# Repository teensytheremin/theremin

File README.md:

# Teensy Theremin

Teensy 4.1 MCU based Digital Theremin

This project is aimed to design of simple but good DIY digital [theremin](https://en.wikipedia.org/wiki/Theremin) based on microcontroller and FPGAs.

Project's documentation is available on [Github Pages](https://teensytheremin.github.io/theremin/)

## Licensing

This is open source open hardware project.

You can freely build device using instructions for personal usage, but cannot sell it.

Firmware is licensed under GPL v2 license.

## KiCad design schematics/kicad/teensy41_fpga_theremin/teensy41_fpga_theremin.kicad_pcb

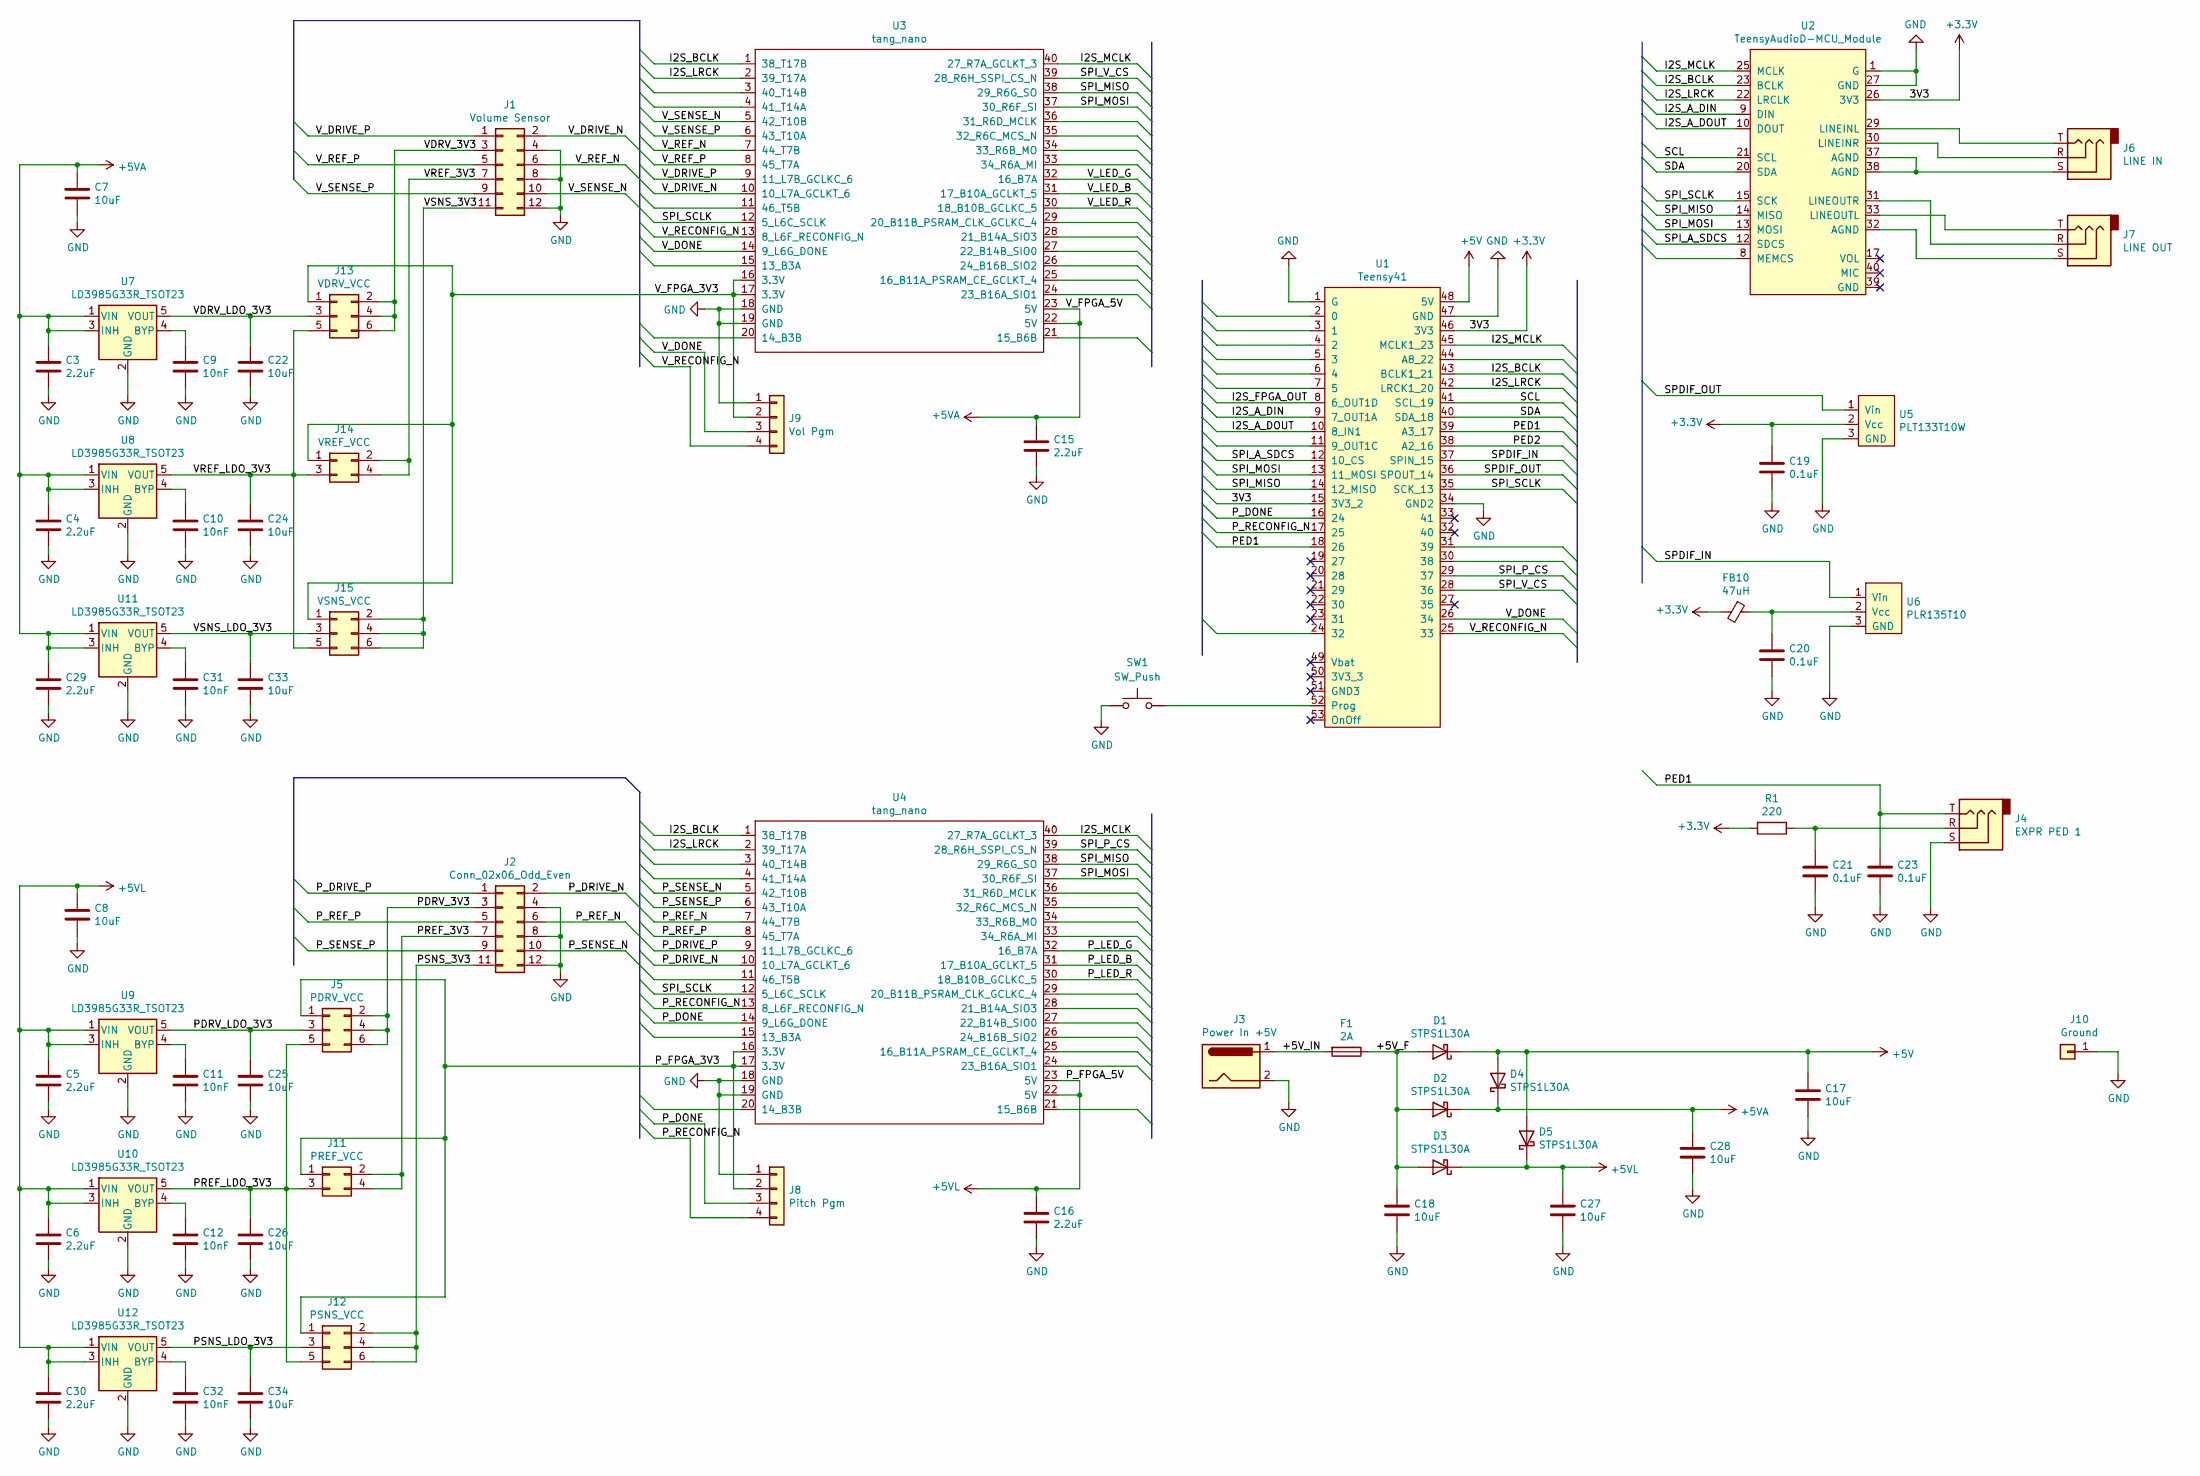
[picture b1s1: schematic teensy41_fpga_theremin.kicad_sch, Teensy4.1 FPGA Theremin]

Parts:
C3, C4, C5, C6, C15, C16, C29, C30: 2.2uF; C_0805_2012Metric
C7, C8, C17, C18, C22, C24, C25, C26, C27, C28, C33, C34: 10uF; C_0805_2012Metric
C9, C10, C11, C12, C31, C32: 10nF; C_0805_2012Metric
C19, C20, C21, C23: 0.1uF; C_0805_2012Metric
D1, D2, D3, D4, D5: STPS1L30A; D_SMA
F1: 2A; Fuse_1206_3216Metric
FB10: 47uH; L_1812_4532Metric
J1: Volume Sensor; PinSocket_2x06_P2.54mm_Horizontal
J2: Conn_02x06_Odd_Even; PinSocket_2x06_P2.54mm_Horizontal
J3: Power In +5V; BarrelJack_Horizontal
J4: EXPR PED 1; Jack_6.35mm_ST_008G_04
J5: PDRV_VCC; PinHeader_2x03_P2.54mm_Vertical
J6: LINE IN; Jack_3.5mm_CUI_SJ1-3533NG_Horizontal
J7: LINE OUT; Jack_6.35mm_ST_008G_04
J8: Pitch Pgm; PinHeader_1x04_P2.54mm_Vertical
J9: Vol Pgm; PinHeader_1x04_P2.54mm_Vertical
J10: Ground; PinHeader_1x01_P2.54mm_Vertical
J11: PREF_VCC; PinHeader_2x02_P2.54mm_Vertical
J12: PSNS_VCC; PinHeader_2x03_P2.54mm_Vertical
J13: VDRV_VCC; PinHeader_2x03_P2.54mm_Vertical
J14: VREF_VCC; PinHeader_2x02_P2.54mm_Vertical
J15: VSNS_VCC; PinHeader_2x03_P2.54mm_Vertical
R1: 220; R_0805_2012Metric
SW1: SW_Push; SW_Tactile_SPST_Angled_PTS645Vx58-2LFS
U1: Teensy41
U2: TeensyAudioD-MCU_Module; TeensyAudioD
U3, U4: tang_nano
U5: PLT133T10W
U6: PLR135T10; PLT133T10W
U7, U8, U9, U10, U11, U12: LD3985G33R_TSOT23; TSOT-23-5

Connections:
+3V3: C19.1, FB10.2, R1.2, U1.15 (3V3_2), U1.46 (3V3), U2.26 (3V3), U5.2 (Vcc)
+5V: C17.1, D1.1 (K), D4.2 (A), D5.2 (A), U1.48 (5V)
+5VA: C3.1, C4.1, C7.1, C15.1, C28.1, C29.1, D2.1 (K), D4.1 (K), U3.22 (5V), U3.23 (5V), U7.1 (VIN), U7.3 (INH), U8.1 (VIN), U8.3 (INH), U11.1 (VIN), U11.3 (INH)
+5VL: C5.1, C6.1, C8.1, C16.1, C27.1, C30.1, D3.1 (K), D5.1 (K), U4.22 (5V), U4.23 (5V), U9.1 (VIN), U9.3 (INH), U10.1 (VIN), U10.3 (INH), U12.1 (VIN), U12.3 (INH)
/+5V_F: C18.1, D1.2 (A), D2.2 (A), D3.2 (A), F1.1
/+5V_IN: F1.2, J3.1
/I2S_A_DIN: U1.9 (7_OUT1A), U2.9 (DIN)
/I2S_A_DOUT: U1.10 (8_IN1), U2.10 (DOUT)
/I2S_BCLK: U1.43 (BCLK1_21), U2.23 (BCLK), U3.1 (38_T17B), U4.1 (38_T17B)
/I2S_FPGA_OUT: U1.8 (6_OUT1D)
/I2S_LRCK: U1.42 (LRCK1_20), U2.22 (LRCLK), U3.2 (39_T17A), U4.2 (39_T17A)
/I2S_MCLK: U1.45 (MCLK1_23), U2.25 (MCLK), U3.40 (27_R7A_GCLKT_3), U4.40 (27_R7A_GCLKT_3)
/PDRV_3V3: J2.3, J5.2, J5.4, J5.6
/PDRV_LDO_3V3: C25.1, J5.3, U9.5 (VOUT)
/PED1: C23.1, J4.T, U1.18 (26), U1.39 (A3_17)
/PED2: U1.38 (A2_16)
/PREF_3V3: J2.7, J11.2, J11.4
/PREF_LDO_3V3: C26.1, J5.5, J11.3, J12.5, U10.5 (VOUT)
/PSNS_3V3: J2.11, J12.2, J12.4, J12.6
/PSNS_LDO_3V3: C34.1, J12.3, U12.5 (VOUT)
/P_DONE: J8.3, U1.16 (24), U4.14 (9_L6G_DONE)
/P_DRIVE_N: J2.2, U4.10 (10_L7A_GCLKT_6)
/P_DRIVE_P: J2.1, U4.9 (11_L7B_GCLKC_6)
/P_FPGA_3V3: J5.1, J8.2, J11.1, J12.1, U4.16 (3.3V), U4.17 (3.3V)
/P_LED_B: U4.31 (17_B10A_GCLKT_5)
/P_LED_G: U4.32 (16_B7A)
/P_LED_R: U4.30 (18_B10B_GCLKC_5)
/P_RECONFIG_N: J8.4, U1.17 (25), U4.13 (8_L6F_RECONFIG_N)
/P_REF_N: J2.6, U4.7 (44_T7B)
/P_REF_P: J2.5, U4.8 (45_T7A)
/P_SENSE_N: J2.10, U4.5 (42_T10B)
/P_SENSE_P: J2.9, U4.6 (43_T10A)
/SCL: U1.41 (SCL_19), U2.21 (SCL)
/SDA: U1.40 (SDA_18), U2.20 (SDA)
/SPDIF_IN: U1.37 (SPIN_15), U6.1 (Vin)
/SPDIF_OUT: U1.36 (SPOUT_14), U5.1 (Vin)
/SPI_A_SDCS: U1.12 (10_CS), U2.12 (SDCS)
/SPI_MISO: U1.14 (12_MISO), U2.14 (MISO), U3.38 (29_R6G_SO), U4.38 (29_R6G_SO)
/SPI_MOSI: U1.13 (11_MOSI), U2.13 (MOSI), U3.37 (30_R6F_SI), U4.37 (30_R6F_SI)
/SPI_P_CS: U1.29 (37), U4.39 (28_R6H_SSPI_CS_N)
/SPI_SCLK: U1.35 (SCK_13), U2.15 (SCK), U3.12 (5_L6C_SCLK), U4.12 (5_L6C_SCLK)
/SPI_V_CS: U1.28 (36), U3.39 (28_R6H_SSPI_CS_N)
/VDRV_3V3: J1.3, J13.2, J13.4, J13.6
/VDRV_LDO_3V3: C22.1, J13.3, U7.5 (VOUT)
/VREF_3V3: J1.7, J14.2, J14.4
/VREF_LDO_3V3: C24.1, J13.5, J14.3, J15.5, U8.5 (VOUT)
/VSNS_3V3: J1.11, J15.2, J15.4, J15.6
/VSNS_LDO_3V3: C33.1, J15.3, U11.5 (VOUT)
/V_DONE: J9.3, U1.26 (34), U3.14 (9_L6G_DONE)
/V_DRIVE_N: J1.2, U3.10 (10_L7A_GCLKT_6)
/V_DRIVE_P: J1.1, U3.9 (11_L7B_GCLKC_6)
/V_FPGA_3V3: J9.2, J13.1, J14.1, J15.1, U3.16 (3.3V), U3.17 (3.3V)
/V_LED_B: U3.31 (17_B10A_GCLKT_5)
/V_LED_G: U3.32 (16_B7A)
/V_LED_R: U3.30 (18_B10B_GCLKC_5)
/V_RECONFIG_N: J9.4, U1.25 (33), U3.13 (8_L6F_RECONFIG_N)
/V_REF_N: J1.6, U3.7 (44_T7B)
/V_REF_P: J1.5, U3.8 (45_T7A)
/V_SENSE_N: J1.10, U3.5 (42_T10B)
/V_SENSE_P: J1.9, U3.6 (43_T10A)
GND: C3.2, C4.2, C5.2, C6.2, C7.2, C8.2, C9.2, C10.2, C11.2, C12.2, C15.2, C16.2, C17.2, C18.2, C19.2, C20.2, C21.2, C22.2, C23.2, C24.2, C25.2, C26.2, C27.2, C28.2, C29.2, C30.2, C31.2, C32.2, C33.2, C34.2, J1.4, J1.8, J1.12, J2.4, J2.8, J2.12, J3.2, J4.S, J8.1, J9.1, J10.1, SW1.1, U1.1 (G), U1.34 (GND2), U1.47 (GND), U2.1 (G), U2.27 (GND), U3.18 (GND), U3.19 (GND), U4.18 (GND), U4.19 (GND), U5.3 (GND), U6.3 (GND), U7.2 (GND), U8.2 (GND), U9.2 (GND), U10.2 (GND), U11.2 (GND), U12.2 (GND)
unnamed: C9.1, U7.4 (BYP)
unnamed: C10.1, U8.4 (BYP)
unnamed: C11.1, U9.4 (BYP)
unnamed: C12.1, U10.4 (BYP)
unnamed: C20.1, FB10.1, U6.2 (Vcc)
unnamed: C21.1, J4.R, R1.1
unnamed: C31.1, U11.4 (BYP)
unnamed: C32.1, U12.4 (BYP)
unnamed: J6.R, U2.30 (LINEINR)
unnamed: J6.S, U2.37 (AGND), U2.38 (AGND)
unnamed: J6.T, U2.29 (LINEINL)
unnamed: J7.R, U2.31 (LINEOUTR)
unnamed: J7.S, U2.32 (AGND)
unnamed: J7.T, U2.33 (LINEOUTL)
unnamed: SW1.2, U1.52 (Prog)

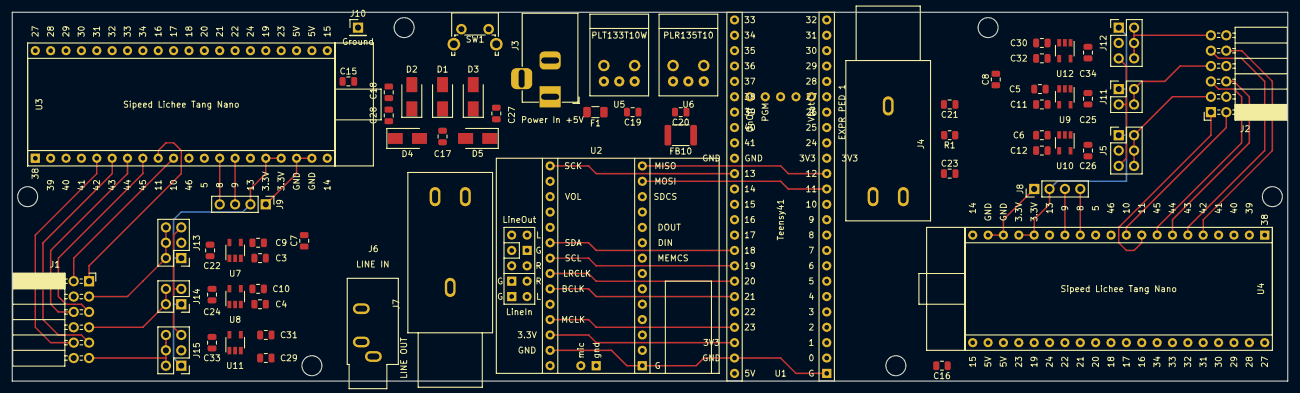
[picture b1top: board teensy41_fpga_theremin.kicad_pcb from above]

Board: 2 copper layers, 210.8 x 61.0 mm, 66 parts (0 on the bottom side), 68 nets.

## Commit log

2021-09-15 Set theme jekyll-theme-tactile
2021-09-15 current sensing comparator sensor simulation
2021-09-15 ltspice model
2021-09-15 sensor page created
2021-09-15 update main page - components to buy
2021-09-15 description
2021-09-15 update description
2021-09-15 config changes
2021-09-15 sensors page
2021-09-15 update sensors page
2021-09-15 ltc6752 oscillator spice model:
2021-09-15 spice model
2021-09-15 add github pages link
2021-09-15 main board kicad project and geerber files
2021-09-16 git ignore for ltspice
2021-09-16 add dester's bjt current sensing oscillator model
2021-09-21 add D flipflop model
2021-09-21 lvc74 lvc86 pll
2021-09-23 pll model
2021-09-24 opamp models, pll schematic
2021-09-27 current sensing pll model
2021-09-27 ltspice simulation
2021-10-11 current sensing oscillator model
2021-10-11 oscillator ltspice images
2021-10-12 current sensing oscillator 04 spice model images
2021-10-12 current sensing oscillator ltspice model 04
2021-10-13 current sensing oscillator 05
2021-10-13 oscillator images 05
2021-10-15 lt6200 current sensing oscillator images
2021-10-15 lt6200 oscillator spice model
2021-10-15 schematics - pdfs and images
2021-10-15 add libraries
2021-10-15 display and controls board
2021-10-15 PCBs
2021-10-15 boards
2021-10-15 sensor pdf links
2021-10-15 update docs
2021-10-16 sensor design
2021-10-22 component spice models
2021-10-22 unbuffered inverter oscillator model
2021-10-22 unbuffered inverter current sensing spice model screenshots
2021-10-27 dual opamps current sensing oscillator model image
2021-10-27 dual opamp current sensing oscillator - ltspice model
2021-10-28 current sensing pll ltspice model
2021-10-28 ltspice component lvc1gx04
2021-10-28 pll oscillator spice model
2021-11-06 current sensing oscillator 8bjts spice model
2021-11-06 oscillator spice model
2021-11-08 pll bjts spice model
2021-11-08 spice model pll oscillator bjts
2021-11-09 current sensing oscillator inverters
2021-11-09 spice model - unbuffered inverters current sensing oscillator
2021-11-10 74hcu04 current sensing oscillator ltspice model
2021-11-10 unbuffered inverter spice models
2021-11-11 inverter spice models
2021-11-11 lvcu04 oscillator ltspice model
2021-11-11 lvcu04 oscillator ltspice model images
2021-11-12 inv and bjt current sensing oscillator model
2021-11-12 current sensing oscillator on inverters and bjt current mirrors - ltspice model
2021-11-17 main hum noise simulation
2021-11-23 xo2 / tinyfpga ax2 theremin sensor implementation - initial commit
2021-11-23 ax2 pins assignment
2021-11-30 teensy fpga cabinet and boards placement / planning
2021-11-30 cabinet drawing
2021-11-30 teensy fpga main board fpga project
2021-11-30 kicad libraries
2021-12-09 cabinet OpenSCAD - part 1
2021-12-09 teensy fpga theremin main pcb
2021-12-09 openscad screenshots
2021-12-10 cabinet design - tablet mounts and antennas
2021-12-10 cabinet images
2021-12-13 openscad cabinet project
2021-12-14 cabinet design - openscad
2021-12-16 tang nano photos
2021-12-16 Initial commit
    A modified PlaySynthMusic example. Testing sound and codec. Prints audio chip id to serial port.
2021-12-17 pcb placement render
2021-12-17 cabinet openscad model:
2021-12-17 Pitch and volume input simulation added
    Using IntervalTimer to simulate pitch and volume input from sensors. Volume control now works. Sensor values are printed to serial port.
2021-12-20 fittings
2021-12-22 Generating sine with changing frequency and volume
    Using AudioSynthWaveformSine to generate sine. Later it has to be changed to a new AudioStream child class.
2021-12-24 cabinet model
2021-12-24 teensytheremin fpga main board kicad project
2021-12-24 openscad cabinet render images
2021-12-28 fpga and sensor schematic, v1
2021-12-28 powr supply kicad
2022-01-10 cabinet opanscad model
2022-01-10 cabinet model openscad fixes
2022-01-10 openscad images
2022-01-11 cabinet - added program tact button
2022-02-09 thereminscore, initial commit
2022-02-09 thereminscore screenshot
2022-02-15 theremin score app, basic drawing working
2022-03-09 update screenshot of thereminscore
2023-03-01 analog front end spice model - DDS current sensing
2023-03-01 dds afe ltspice model
2023-03-01 dds sensor images
2023-03-01 dds sine drive phase shift sensor ltspice simulation results
2023-03-14 wallin oscillator BJTs diff cascade power rails sensing LTSpice model
2023-03-14 wallin oscillator bjt power rail sensing ltspice model images
2023-03-17 wallin oscillator on bjt differential amp with current mirror load
2023-03-17 wallin oscillator ltspice model images - diff amp with current mirror load
2023-03-19 current sensing oscillator diff cascade ltspice simulation
2023-03-19 current sensing oscillator ltspice model
2023-03-22 current sensing theremin oscillator - voltage follower buffer - ltspice model
2023-03-22 current sensing theremin oscillator - voltage follower buffer - ltspice screenshots
2023-03-22 voltage follower current sensing buffer - ltspice model:
2023-03-22 ltspice model images - voltage follower buffer for current sensing
2023-04-04 transconductance amplifier current sensing buffer ltspice model
2023-04-04 OTA volt follower buffer ltspice model
2023-04-10 bjt OTA mixer ltspice model
2023-04-10 bjt ota analog theremin mixer ltspice model
2023-04-10 mixer and volume control VCA for theremin - OTA based - ltspice model
2023-04-10 mixer with volume control - ltspice model
2023-04-10 update images
2023-04-15 ltspice model of 2 x OTA current sensing oscillator
2023-04-15 current sensing oscillator on dual OTA ltspice model images
